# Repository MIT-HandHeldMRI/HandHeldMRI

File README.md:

# 64800_MRI
Designs for the 3D printed tabletop MRI for 6.4800: Biomedical Imaging with MRI

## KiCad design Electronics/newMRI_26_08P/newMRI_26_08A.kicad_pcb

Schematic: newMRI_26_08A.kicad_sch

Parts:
C1: JR500HV; CAP-SMD_L3.5-W3.1_V-7586; MPN JR500HV; LCSC Part C20342596
C2, C32, C34: 22u35V; CAP_GMK325B7155MN-T_TAY; LCSC Part C6120016
C3, C25, C26, C27, C35: 15nf; C0402; MPN CC0402JRX7R7BB153; LCSC Part C527002
C5, C6, C7, C8, C31, C36, C40, C41, C42: C1u25v; C0603; MPN CL10B105KA8NNNC; LCSC Part C29936
C9, C19, C20, C21, C1002, C1004, C1005, C1010, C1011, C1012, C1013, C1016, C1018, C1019, C1020, C1021, C1023, C1025, C1027, C1029, C1031, C1033, C1035, C1037, C1039, C1041, C1043, C1047, C1052, C1063, C1064, C1065, C1067, C1068, C1071, C1073, C1075, C1077, C1078, C1079, C1087, C1092, C1093, C1094, C1095, C1097, C1100: 10u25v; C0603; MPN GRM188R61E106KA73D; LCSC Part C344022
C10, C12, C13, C14, C15, C16, C17, C18, C1003, C1006, C1007, C1008, C1009, C1014, C1015, C1017, C1022, C1024, C1026, C1028, C1030, C1032, C1034, C1036, C1038, C1040, C1042, C1044, C1046, C1048, C1050, C1055, C1066, C1070, C1072, C1074, C1076, C1080, C1081, C1082, C1083, C1084, C1085, C1086, C1088, C1089, C1090, C1091, C1096, C1098, C1099, C1109, C1110, C1111, C1112, C1113, C1114, C1115, C1116, C1117, C1118: 0.1u; C0402; MPN CC0402JRX7R9BB104; LCSC Part C5182432
C22, C23, C29, C30: 220PF; C0805; MPN CC0805JRNPOBBN221; LCSC Part C576977
C24, C28: 270pf250V; C0805; MPN 0805CG271J251NT; LCSC Part C20606779; not fitted
C33, C37, C38, C39, C43, C44, C45, C46, C47: 22u35V; CAP_GMK325B7155MN-T_TAY; LCSC Part C6120017
C1001: JR500HV; CAP-SMD_L3.5-W3.1_V-7586; MPN JR500HV; LCSC Part C20342596; not fitted
C1045, C1049, C1051, C1054: 0.1u; C0402; MPN CC0402JRX7R9BB104; LCSC Part C5182432; not fitted
C1053, C1062: 4.7nf; C0402; MPN GRM1555C1H472JE01D; LCSC Part C1518204
C1056, C1057, C1059, C1061: 680pf; C0402; MPN CC0402JRNPO9BN681; LCSC Part C113781
C1058, C1060: 1.5nf; C0603; MPN CC0603JRNPO9BN152; LCSC Part C107039
C1069, C1101: 47pf; C0805; MPN GRM21A5C2E470JW01D; LCSC Part C2179874
C1103, C1104, C1105, C1106: 150pf250V; C0805; MPN TCC0805COG151J251BT; LCSC Part C282715
CN1: 1755765; CONN-TH_1755765; MPN 1755765; LCSC Part C480542
CN2, CN3: DF40C-80DP-0.4V; CONN-SMD_DF40C-80DP-0.4V-51; MPN DF40C-80DP-0.4V(51); LCSC Part C294544
CN4: DF40C-50DP-0.4V; CONN-SMD_DF40C-50DP-0.4V; MPN DF40C-50DP-0.4V(51); LCSC Part C424645
CR1: L79L05; SOIC-8_L5.0-W4.0-P1.27-LS6.0-BL; LCSC Part C2802525
D1, D3, D1001, D1002, D1003, D1004: DIO15A; POWERDI-5_L5.4-W4.0-LS6.5-RD; MPN SBRT15U50SP5-13; LCSC Part C211388
D2, D4, D5, D6, D7, D8, D9, D10, D11, D12, D13, D14, D15, D16, D17, D18: DIOS3A; SMA_L4.3-W2.6-LS5.2-RD; MPN SK36A-LTP; LCSC Part C106867
J1, J4: H3161-05; HARWIN_H3161-05; PARTREV 20; LCSC Part C17274599
J2, J3: H3161-05; HARWIN_H3161-05; PARTREV 20; LCSC Part C17274599; not fitted
L2, L3: Ferrite; L0805; MPN MPZ2012S221AT000; LCSC Part C76818
L1002, L1003: NLCV32T-150K-EF; IND-SMD_L3.2-W2.5; MPN NLCV32T-150K-EF; LCSC Part C250232; not fitted
L1004, L1005: NLCV32T-150K-EF; IND-SMD_L3.2-W2.5; MPN NLCV32T-150K-EF; LCSC Part C250232
L1008, L1009: 820nh; L_1210_3225Metric; MPN NLV32T-R82J-EF; LCSC Part C295116
L1010, L1012, L1013, L1014: 1.8uh; L_1210_3225Metric; MPN NLV32T-1R8J-PF; LCSC Part C41039
R1, R12: 355033RJT; RES_3550_TEC; LCSC Part C4048132
R2, R9, R10, R11: 2R6W; RES_3560_TEC; LCSC Part C2096258
R3, R4, R5, R6, R7, R8: 0.05,1W; RC1206N_VIS; LCSC Part C2073508
R15, R16: 220; R0402; MPN 0402WGF2200TCE; LCSC Part C25091
R17, R18, R19: 49.9; R0402; MPN RMC040249.91%N; LCSC Part C325388
R1001, R1005, R1007, R1009, R1010, R1011, R1012, R1013, R1016, R1017, R1018, R1021, R1026, R1027, R1028, R1033: 10K; R0402; MPN CRCW040210K0FKED; LCSC Part C71617
R1002, R1003, R1019, R1020: FBF25FP-R250; R2512; MPN FBF25FP-R250; LCSC Part C395975
R1004, R1043: 4K7; R0402; MPN RC0402FR-074K7L; LCSC Part C105871
R1006, R1015, R1029, R1030: 4K7; R0402; MPN RC0402FR-074K7L; LCSC Part C105871; not fitted
R1008, R1014, R1022, R1023, R1024, R1025, R1031, R1032, R1034, R1044, R1045, R1047, R1048, R1049: 1K5; R0402; MPN RC0402FR-071K5L; LCSC Part C114759
R1035, R1036, R1037, R1038, R1039, R1040, R1041, R1042: 0402WGF1501TCE; R0402; MPN 0402WGF1501TCE; LCSC Part C25867
RF1, RF2, RF1001: 5-1814832-2; SMA-TH_5-1814832-2; MPN 5-1814832-2; LCSC Part C482015
U1, U4, U8: AD8274ARMZ; RM_8_ADI-L
U2: AFE5808AZCF; BGA-135_L15.0-W9.0-R15-C9-P1.00-BL; MPN AFE5808AZCF; LCSC Part C528615
U3: MAX14808ETK+T; 21-0142E_T6800-4_MXM-L; LCSC Part C2156340
U5, U6: X6511FV-24-C85D32; HDR-TH_24P-P2.54-V-F; MPN X6511FV-24-C85D32; LCSC Part C2883741
U7, U9, U10, U1001, U1002, U1003: OPA548FKTWT; KTW0007A; LCSC Part C2687965
U13, U1004, U1005, U1006: PHA-13LN+; SOT-89-3_L4.5-W2.5-P1.50-LS4.2-BR; MPN PHA-13LN+; LCSC Part C3008204
U14: TPS7A2118PQWDSGRQ1; WSON-8_L2.0-W2.0-P0.50-TL-EP; MPN TPS7A2118PQWDSGRQ1; LCSC Part C41487852
U15, U19: TPS7A2133PQWDRBRQ1; DFN-8_L3.0-W3.0-P0.65-BL-EP-2; MPN TPS7A2133PQWDRBRQ1; LCSC Part C21285173
U17: LM78L05; SOIC-8_L4.9-W3.9-P1.27-LS6.0-BL; MPN LM78L05ACMX/NOPB; LCSC Part C373350
U18: DAC7564; PW0016A_N; LCSC Part C2866362
U1007, U1008, U1009, U1010, U1011, U1012: 215307-3; 215307-3_TYC; LCSC Part C239343

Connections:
5VD: C44.2, C45.2, C46.2, C47.2, C1072.2, C1073.1, C1074.2, C1075.1, C1090.2, CN1.3, CN4.36, CN4.38, CN4.40, CN4.42, CN4.44, CN4.46, CN4.48, CN4.50, U6.1, U14.5 (EN), U14.7 (IN), U14.8 (IN), U15.5 (EN), U15.8 (IN)
+5VA: C1040.2, C1041.1, C1042.2, C1043.1, C1046.2, C1047.1, C1050.2, C1052.1, C1063.1, C1087.1, C1091.2, CN1.4, L1002.2, L1003.2, L1004.2, L1005.2, U2.K2 (AVDD_5V)
+15V: C2.1, C32.1, C33.1, C34.1, C1002.2, C1003.2, C1005.2, C1014.2, C1015.2, C1016.2, C1017.2, C1019.2, C1022.2, C1023.2, C1024.2, C1025.2, C1026.2, C1027.2, C1064.1, C1068.2, C1089.2, C1094.2, C1095.2, C1116.1, C1117.1, C1118.1, CN1.1, D3.3 (C), D8.1 (K), D11.1 (K), D15.1 (K), D18.1 (K), U1.7 (VS+), U4.7 (VS+), U7.5 (V+), U7.7 (E_S), U8.7 (VS+), U9.5 (V+), U9.7 (E_S), U10.5 (V+), U10.7 (E_S), U17.8 (VIN), U1001.5 (V+), U1001.7 (E_S), U1002.5 (V+), U1002.7 (E_S), U1003.5 (V+), U1003.7 (E_S)
-15V: C37.2, C38.2, C39.2, C43.2, C1009.2, C1013.1, C1028.2, C1029.2, C1030.2, C1031.2, C1032.2, C1033.2, C1034.2, C1035.2, C1036.2, C1037.2, C1038.2, C1039.2, C1065.1, C1067.2, C1088.2, C1092.2, C1093.2, C1113.2, C1114.2, C1115.2, CN1.2, CR1.2 (VIN), CR1.3 (VIN), CR1.6 (VIN), CR1.7 (VIN), D1.1 (A), D1.2 (A), D7.2 (A), D14.2 (A), D16.2 (A), D17.2 (A), R1005.1, R1007.2, R1010.1, R1016.1, R1017.1, R1026.1, U1.4 (VS-), U4.4 (VS-), U7.4 (V-), U7.8 (TAB), U8.4 (VS-), U9.4 (V-), U9.8 (TAB), U10.4 (V-), U10.8 (TAB), U1001.4 (V-), U1001.8 (TAB), U1002.4 (V-), U1002.8 (TAB), U1003.4 (V-), U1003.8 (TAB)
/1P8A: L3.2, U2.J6 (AVDD_ADC), U2.J7 (AVDD_ADC), U2.K8 (AVDD_ADC), U2.L3 (AVDD_ADC), U2.M1 (AVDD_ADC), U2.M2 (AVDD_ADC)
/1P8D: C1070.2, C1071.1, L3.1, U2.N3 (DVDD), U2.N7 (DVDD), U14.1 (OUT), U14.2 (OUT)
/3A3: CN4.37
/3P3A: L2.2, U2.A1 (AVDD), U2.D8 (AVDD), U2.D9 (AVDD), U2.E8 (AVDD), U2.E9 (AVDD), U2.K1 (AVDD)
/3P3D: C1076.2, C1077.1, L2.1, U15.1 (OUT)
/A10: U5.16, U1007.2, U1007.5
/A11: U5.17, U1010.2, U1010.5
/A12: U5.18, U1008.2, U1008.5
/A13: U5.19, U1009.2, U1009.5
/ACT1: C31.2, U2.B9 (ACT1)
/ACT2: C36.2, U2.B8 (ACT2)
/ACT7: C41.2, U2.B3 (ACT7)
/ACT8: C42.2, U2.B2 (ACT8)
/ADCCLK: R17.1, U6.14
/AR: R1036.1
/BR: R1035.1
/CE: U2.L9 (SEN), U6.21
/CLKP_ADC: R17.2, U2.L1 (CLKP_ADC)
/D2: CN2.54, RF2.5, U5.4
/D3: CN2.55, U5.5
/D4: CN2.57, U5.6
/D5: CN2.58, U5.7
/D6: CN2.60, U5.8
/D7: CN2.27, U5.9
/D8: CN2.26, U5.10
/D9: CN2.24, U5.11
/D10: CN2.23, U5.12
/D11: CN2.21, U5.13
/D12: CN2.20, U5.14
/DACA: U9.1 (VIN+), U18.1 (VOUTA)
/DACB: U18.2 (VOUTB), U1002.1 (VIN+)
/DACC: R1023.1, U18.7 (VOUTC)
/DACD: R1022.1, U18.8 (VOUTD)
/DACDIN: U5.20, U18.11 (DIN)
/DACREF: C1096.2, C1097.2, R1014.1, R1024.1, U18.3 (VREFH_VREFOUT)
/DACSCLK: U5.22, U18.10 (SCLK)
/DD1M: CN2.6, U2.N8 (D1M)
/DD1P: CN2.5, U2.N9 (D1P)
/DD2M: CN2.9, U2.P9 (D2M)
/DD2P: CN2.8, U2.R9 (D2P)
/DD6M: CN2.11, U2.P2 (D6M)
/DD6P: CN2.12, U2.R2 (D6P)
/DD7M: CN2.14, U2.P1 (D7M)
/DD7P: CN2.15, U2.R1 (D7P)
/DD8M: CN2.70, U2.N2 (D8M)
/DD8P: CN2.69, U2.N1 (D8P)
/DDCLKM: CN2.76, U2.P6 (DCLKM)
/DDCLKP: CN2.75, U2.R6 (DCLKP)
/DDFCLKM: CN2.73, U2.P4 (FCLKM)
/DDFCLKP: CN2.72, U2.R4 (FCLKP)
/DINN1: U3.65 (DINN1), U6.11
/DINN2: U3.63 (DINN2), U6.13
/DINN3: U3.61 (DINN3), U6.17
/DINN4: U3.59 (DINN4), U6.19
/DINN5: U3.21 (DINN5), U6.8
/DINN6: U3.23 (DINN6), U6.6
/DINN7: U3.25 (DINN7), U6.4
/DINN8: U3.27 (DINN8), U5.3
/DINP1: U3.66 (DINP1), U6.10
/DINP2: U3.64 (DINP2), U6.12
/DINP3: U3.62 (DINP3), U6.16
/DINP4: U3.60 (DINP4), U6.18
/DINP5: U3.20 (DINP5), U6.9
/DINP6: U3.22 (DINP6), U6.7
/DINP7: U3.24 (DINP7), U6.5
/DINP8: U3.26 (DINP8), U5.2
/GRADA: C40.1, C1098.1, U8.5 (SENSE), U8.6 (OUT)
/GRADB: C41.1, C1083.1, U4.5 (SENSE), U4.6 (OUT)
/GRADC: C42.1, C1084.1, U1.5 (SENSE), U1.6 (OUT)
/LVOUT3: R19.2, U3.3 (LVOUT3)
/LVOUT4: C1062.1, U3.4 (LVOUT4)
/LVOUT5: C1053.1, U3.14 (LVOUT5)
/LVOUT6: R18.2, U3.15 (LVOUT6)
/LVOUT7: C1111.2, U3.16 (LVOUT7)
/LVOUT8: C1112.2, U3.17 (LVOUT8)
/N5VLT: C1006.1, C1012.1, CR1.1 (VOUT), U3.29 (VEE), U3.57 (VEE)
/NSYNC: U5.23, U18.9 (SYNC_N)
/OUT1: C1103.2, R9.2, R1039.2, U3.51 (OUT1)
/OUT2: C1106.2, R10.2, R1042.2, U3.49 (OUT2)
/OUT3/RFA-: C23.2, C28.2, C30.1, C1001.2, J2.1 (1_1), R1021.2, U3.47 (OUT3)
/OUT4: C1101.2, U3.45 (OUT4)
/OUT5: C1069.2, U3.41 (OUT5)
/OUT6/RFB-: C1.2, C22.1, C24.1, C29.2, J1.1 (1_1), R1033.1, U3.39 (OUT6)
/OUT7: C1104.2, R2.2, R1040.2, U3.37 (OUT7)
/OUT8: C1105.2, R11.2, R1041.2, U3.35 (OUT8)
/P3P3: C1007.2, C1011.1, R1038.1, U3.19 (VDD), U3.67 (VDD), U19.1 (OUT)
/P5VLT: C1008.2, C1010.1, C1048.2, C1066.2, U3.28 (VCC), U3.58 (VCC), U17.1 (VOUT), U19.5 (EN), U19.8 (IN)
/RESET: U2.H9 (RESET), U6.24
/RFA: C36.1, C1057.2, C1085.1, RF1001.5
/RFA+: C23.1, C28.1, C1001.1, C1101.1, J3.1 (1_1)
/RFB: C31.1, C1059.2, C1086.1, RF1.5
/RFB+: C1.1, C22.2, C24.2, C1069.1, J4.1 (1_1)
/SCLK: U2.J9 (SCLK), U6.23
/SDATA: U2.K9 (SDATA), U6.22
/SDOUT: U2.M9 (SDOUT), U6.20
/VDD: C1099.2, C1100.2, U5.15, U18.4 (AVDD), U18.12 (IOVDD), U1007.1, U1007.6, U1008.1, U1008.6, U1009.1, U1009.6, U1010.1, U1010.6
/VNNA: C8.1, C9.2, C12.1, C14.1, C1021.1, D4.2 (A), D13.2 (A), D17.1 (K), D1002.1 (A), D1002.2 (A), R1002.2, U3.44 (VNNA), U3.48 (VNNA), U3.52 (VNNA)
/VNNB: C5.1, C15.1, C17.1, C20.2, C1020.2, D6.2 (A), D12.2 (A), D16.1 (K), D1001.1 (A), D1001.2 (A), R1019.2, U3.34 (VNNB), U3.38 (VNNB), U3.42 (VNNB)
/VOPA: R12.1, R1027.1, U7.6 (VO)
/VOPAP: D7.1 (K), D8.2 (A), R12.2, U1012.4
/VOPA_B: R5.1, R6.1, R1034.2, R1049.2, U1.2 (IN-)
/VOPA_B+: R5.2, U1.3 (IN+), U1012.3
/VOPB: R1.1, R1028.1, U1003.6 (VO)
/VOPBP: D11.2 (A), D14.1 (K), R1.2, U1011.6
/VOUT1P: D10.2 (A), D13.1 (K), R9.1, U1012.6
/VOUT1_2: R3.1, R8.1, R1031.2, R1047.2, U8.2 (IN-)
/VOUT1_2+: R3.2, U8.3 (IN+), U1012.1
/VOUT2P: D2.2 (A), D4.1 (K), R10.1, U1011.4
/VOUT7P: D9.2 (A), D12.1 (K), R2.1, U1012.5
/VOUT7_8: R4.1, R7.1, R1032.2, R1048.2, U4.2 (IN-)
/VOUT7_8+: R4.2, U4.3 (IN+), U1012.2
/VOUT8P: D5.2 (A), D6.1 (K), R11.1, U1011.5
/VPPA: C7.1, C10.1, C13.1, C19.2, C1004.2, D2.1 (K), D10.1 (K), D18.2 (A), D1003.3 (C), R1003.2, U3.46 (VPPA), U3.50 (VPPA), U3.54 (VPPA)
/VPPB: C6.1, C16.1, C18.1, C21.2, C1018.2, D5.1 (K), D9.1 (K), D15.2 (A), D1004.3 (C), R1020.2, U3.32 (VPPB), U3.36 (VPPB), U3.40 (VPPB)
GNDREF: C2.2, C3.1, C9.1, C10.2, C12.2, C13.2, C14.2, C15.2, C16.2, C17.2, C18.2, C19.1, C20.1, C21.1, C25.1, C26.1, C27.1, C29.1, C30.2, C32.2, C33.2, C34.2, C35.1, C37.1, C38.1, C39.1, C43.1, C44.1, C45.1, C46.1, C47.1, C1002.1, C1003.1, C1004.1, C1005.1, C1006.2, C1007.1, C1008.1, C1009.1, C1010.2, C1011.2, C1012.2, C1013.2, C1014.1, C1015.1, C1016.1, C1017.1, C1018.1, C1019.1, C1020.1, C1021.2, C1022.1, C1023.1, C1024.1, C1025.1, C1026.1, C1027.1, C1028.1, C1029.1, C1030.1, C1031.1, C1032.1, C1033.1, C1034.1, C1035.1, C1036.1, C1037.1, C1038.1, C1039.1, C1040.1, C1041.2, C1042.1, C1043.2, C1046.1, C1047.2, C1048.1, C1050.1, C1052.2, C1058.2, C1060.2, C1063.2, C1064.2, C1065.2, C1066.1, C1067.1, C1068.1, C1070.1, C1071.2, C1072.1, C1073.2, C1074.1, C1075.2, C1076.1, C1077.2, C1078.2, C1079.2, C1080.1, C1081.1, C1082.1, C1087.2, C1088.1, C1089.1, C1090.1, C1091.1, C1092.1, C1093.1, C1094.1, C1095.1, C1096.1, C1097.1, C1099.1, C1100.1, C1103.1, C1104.1, C1105.1, C1106.1, C1109.1, C1110.1, C1111.1, C1112.1, C1113.1, C1114.1, C1115.1, C1116.2, C1117.2, C1118.2, CN1.5, CN2.1, CN2.4, CN2.7, CN2.10, CN2.13, CN2.16, CN2.19, CN2.22, CN2.25, CN2.28, CN2.31, CN2.34, CN2.37, CN2.40, CN2.41, CN2.44, CN2.47, CN2.50, CN2.53, CN2.56, CN2.59, CN2.62, CN2.65, CN2.68, CN2.71, CN2.74, CN2.77, CN2.80, CN2.81, CN2.82, CN2.83, CN2.84, CN3.81, CN3.82, CN3.83, CN3.84, CN4.24, CN4.26, CN4.28, CN4.30, CN4.32, CN4.34, CN4.51, CN4.52, CN4.53, CN4.54, CR1.5 (GND), D1.3 (C), D3.1 (A), D3.2 (A), D1001.3 (C), D1002.3 (C), D1003.1 (A), D1003.2 (A), D1004.1 (A), D1004.2 (A), L1008.1, L1009.1, R15.2, R16.2, R18.1, R19.1, R1004.1, R1008.1, R1021.1, R1025.1, R1031.1, R1032.1, R1033.2, R1034.1, R1037.1, R1039.1, R1040.1, R1041.1, R1042.1, R1043.1, R1044.2, R1045.1, R1047.1, R1048.1, R1049.1, RF1.1, RF1.2, RF1.3, RF1.4, RF2.1, RF2.2, RF2.3, RF2.4, RF1001.1, RF1001.2, RF1001.3, RF1001.4, U1.1 (REF), U2.C1 (AVSS), U2.D1 (AVSS), U2.D2 (AVSS), U2.D3 (AVSS), U2.D4 (AVSS), U2.D5 (AVSS), U2.D6 (AVSS), U2.D7 (AVSS), U2.E3 (AVSS), U2.E4 (AVSS), U2.E5 (AVSS), U2.E6 (AVSS), U2.E7 (AVSS), U2.F3 (AVSS), U2.F4 (AVSS), U2.F5 (AVSS), U2.F6 (AVSS), U2.F7 (AVSS), U2.G1 (AVSS), U2.G2 (AVSS), U2.G3 (AVSS), U2.G4 (AVSS), U2.G5 (AVSS), U2.G6 (AVSS), U2.G7 (AVSS), U2.H3 (AVSS), U2.H4 (AVSS), U2.H5 (AVSS), U2.H6 (AVSS), U2.H7 (AVSS), U2.H8 (PDN_GLOBAL), U2.J3 (AVSS), U2.J4 (AVSS), U2.J5 (AVSS), U2.J8 (PDN_VCA), U2.K6 (AVSS), U2.L2 (CLKM_ADC), U2.L8 (PDN_ADC), U2.N5 (DVSS), U2.P5 (DVSS), U2.R5 (DVSS), U3.5 (*LDO_EN), U3.7 (SYNC), U3.9 (*CLK), U3.10 (CC0), U3.11 (CC1), U3.13 (MODE1), U3.18 (GND), U3.33 (GND), U3.43 (GND), U3.53 (GND), U3.68 (GND), U3.69 (EPAD), U4.1 (REF), U5.1, U6.2, U6.15, U8.1 (REF), U13.2 (GND), U14.4 (GND), U14.9 (EP), U15.4 (GND), U15.9 (EP), U17.2 (GND), U17.3 (GND), U17.6 (GND), U17.7 (GND), U18.5 (VREFL), U18.6 (GND), U18.13 (A0), U18.14 (A1), U18.15 (ENABLE_N), U18.16 (LDAC), U19.4 (GND), U19.9 (EP), U1004.2 (GND), U1005.2 (GND), U1006.2 (GND), U1007.3, U1007.4, U1008.3, U1008.4, U1009.3, U1009.4, U1010.3, U1010.4
unnamed: C1045.1, R1006.2
unnamed: C1049.1, R1015.2
unnamed: C1051.1, R1030.2
unnamed: C1054.1, R1029.2
unnamed: C1056.2, L1012.1
unnamed: C1057.1, L1010.2
unnamed: C1058.1, L1008.2, L1012.2, L1013.1
unnamed: C1059.1, L1013.2
unnamed: C1060.1, L1009.2, L1010.1, L1014.2
unnamed: C1061.2, L1014.1
unnamed: CN4.12, R1036.2
unnamed: CN4.14, R1035.2
unnamed: R6.2, U1011.1
unnamed: R7.2, U1011.2
unnamed: R8.2, U1011.3
unnamed: C40.2, U2.B4 (ACT6)
unnamed: C1078.1, U2.B1 (CM_BYP)
unnamed: C1080.2, R15.1, U2.K4 (VCNTLM)
unnamed: C1081.2, R16.1, U2.K3 (VCNTLP)
unnamed: C1079.1, U2.K5 (VHIGH)
unnamed: C1082.2, U2.M3 (VREF_IN)
unnamed: C27.2, U2.C9 (INM1)
unnamed: C26.2, U2.C8 (INM2)
unnamed: C35.2, U2.C4 (INM6)
unnamed: C25.2, U2.C3 (INM7)
unnamed: C3.2, U2.C2 (INM8)
unnamed: C1086.2, U2.A9 (INP1)
unnamed: C1085.2, U2.A8 (INP2)
unnamed: C1098.2, U2.A4 (INP6)
unnamed: C1083.2, U2.A3 (INP7)
unnamed: C1084.2, U2.A2 (INP8)
unnamed: R1037.2, U3.8 (CLK)
unnamed: C1109.2, U3.1 (LVOUT1)
unnamed: C1110.2, U3.2 (LVOUT2)
unnamed: R1038.2, U3.12 (MODE0)
unnamed: C8.2, U3.56 (VGNA)
unnamed: C5.2, U3.30 (VGNB)
unnamed: C7.2, U3.55 (VGPA)
unnamed: C6.2, U3.31 (VGPB)
unnamed: R1010.2, U7.3 (ILIM)
unnamed: R1023.2, U7.1 (VIN+)
unnamed: R1024.2, R1027.2, R1044.1, U7.2 (VIN-)
unnamed: R1005.2, U9.3 (ILIM)
unnamed: R1011.1, R1045.2, U9.2 (VIN-)
unnamed: R1003.1, R1011.2, R1012.1, U9.6 (VO)
unnamed: R1007.1, U10.3 (ILIM)
unnamed: R1043.2, U10.1 (VIN+)
unnamed: R1012.2, R1013.2, U10.2 (VIN-)
unnamed: R1002.1, R1013.1, U10.6 (VO)
unnamed: C1055.2, R1030.1, U13.1 (RF-IN)
unnamed: C1051.2, C1056.1, L1004.1, U13.3 (RF-OUT&DC-IN)
unnamed: R1017.2, U1001.3 (ILIM)
unnamed: R1004.2, U1001.1 (VIN+)
unnamed: R1001.2, R1018.2, U1001.2 (VIN-)
unnamed: R1018.1, R1019.1, U1001.6 (VO)
unnamed: R1016.2, U1002.3 (ILIM)
unnamed: R1008.2, R1009.1, U1002.2 (VIN-)
unnamed: R1001.1, R1009.2, R1020.1, U1002.6 (VO)
unnamed: R1026.2, U1003.3 (ILIM)
unnamed: R1022.2, U1003.1 (VIN+)
unnamed: R1014.2, R1025.2, R1028.2, U1003.2 (VIN-)
unnamed: C1044.2, R1006.1, U1004.1 (RF-IN)
unnamed: C1045.2, C1061.1, L1002.1, U1004.3 (RF-OUT&DC-IN)
unnamed: C1062.2, R1015.1, U1005.1 (RF-IN)
unnamed: C1044.1, C1049.2, L1003.1, U1005.3 (RF-OUT&DC-IN)
unnamed: C1053.2, R1029.1, U1006.1 (RF-IN)
unnamed: C1054.2, C1055.1, L1005.1, U1006.3 (RF-OUT&DC-IN)

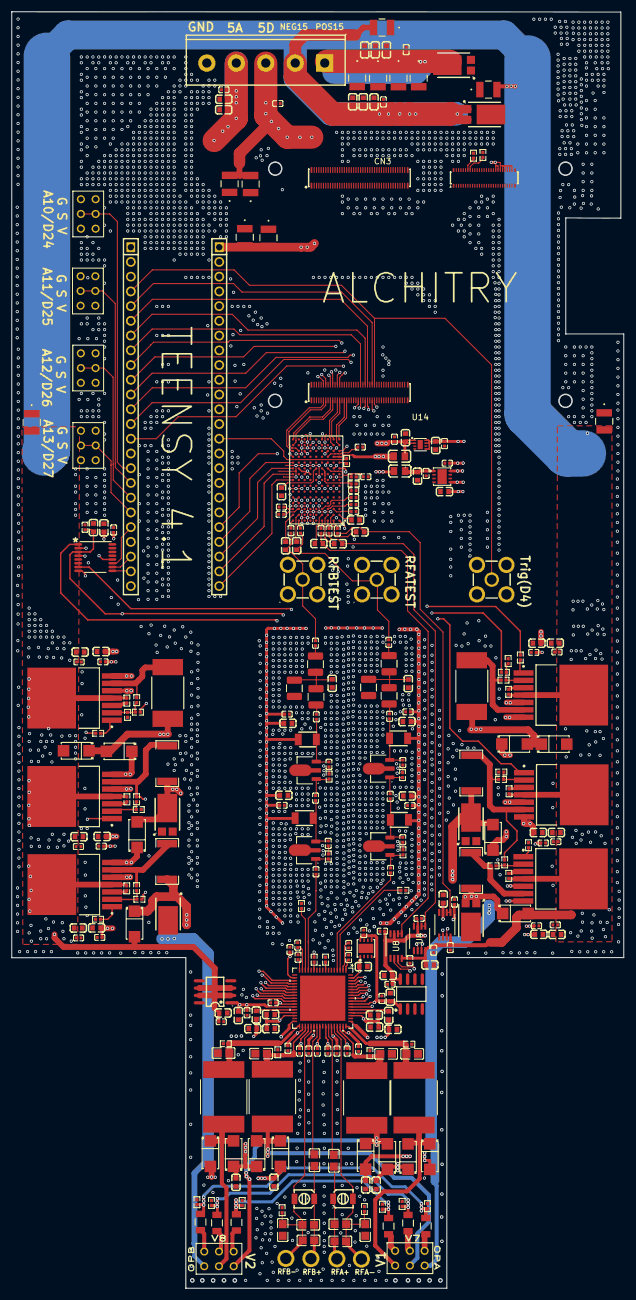
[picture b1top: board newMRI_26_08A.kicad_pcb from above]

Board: 4 copper layers, 105.5 x 220.0 mm, 299 parts (0 on the bottom side), 183 nets.

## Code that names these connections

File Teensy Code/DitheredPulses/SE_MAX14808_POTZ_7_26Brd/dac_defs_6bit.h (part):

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
// 8 Bits to start: setting command, DAC:A,B,C,D
#define CMD  DAC0 DAC0 DAC0 DAC1
#define DACA DAC0 DAC0 DAC0 DAC0
#define DACB DAC0 DAC0 DAC1 DAC0
#define DACC DAC0 DAC1 DAC0 DAC0
#define DACD DAC0 DAC1 DAC1 DAC0

// SETA controls channels 1-4, SETB 5-8, DACC and DACD control opamps
#define SETA DACS CMD DACA
#define SETB DACS CMD DACB
#define SETC DACS CMD DACC
#define SETD DACS CMD DACD

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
